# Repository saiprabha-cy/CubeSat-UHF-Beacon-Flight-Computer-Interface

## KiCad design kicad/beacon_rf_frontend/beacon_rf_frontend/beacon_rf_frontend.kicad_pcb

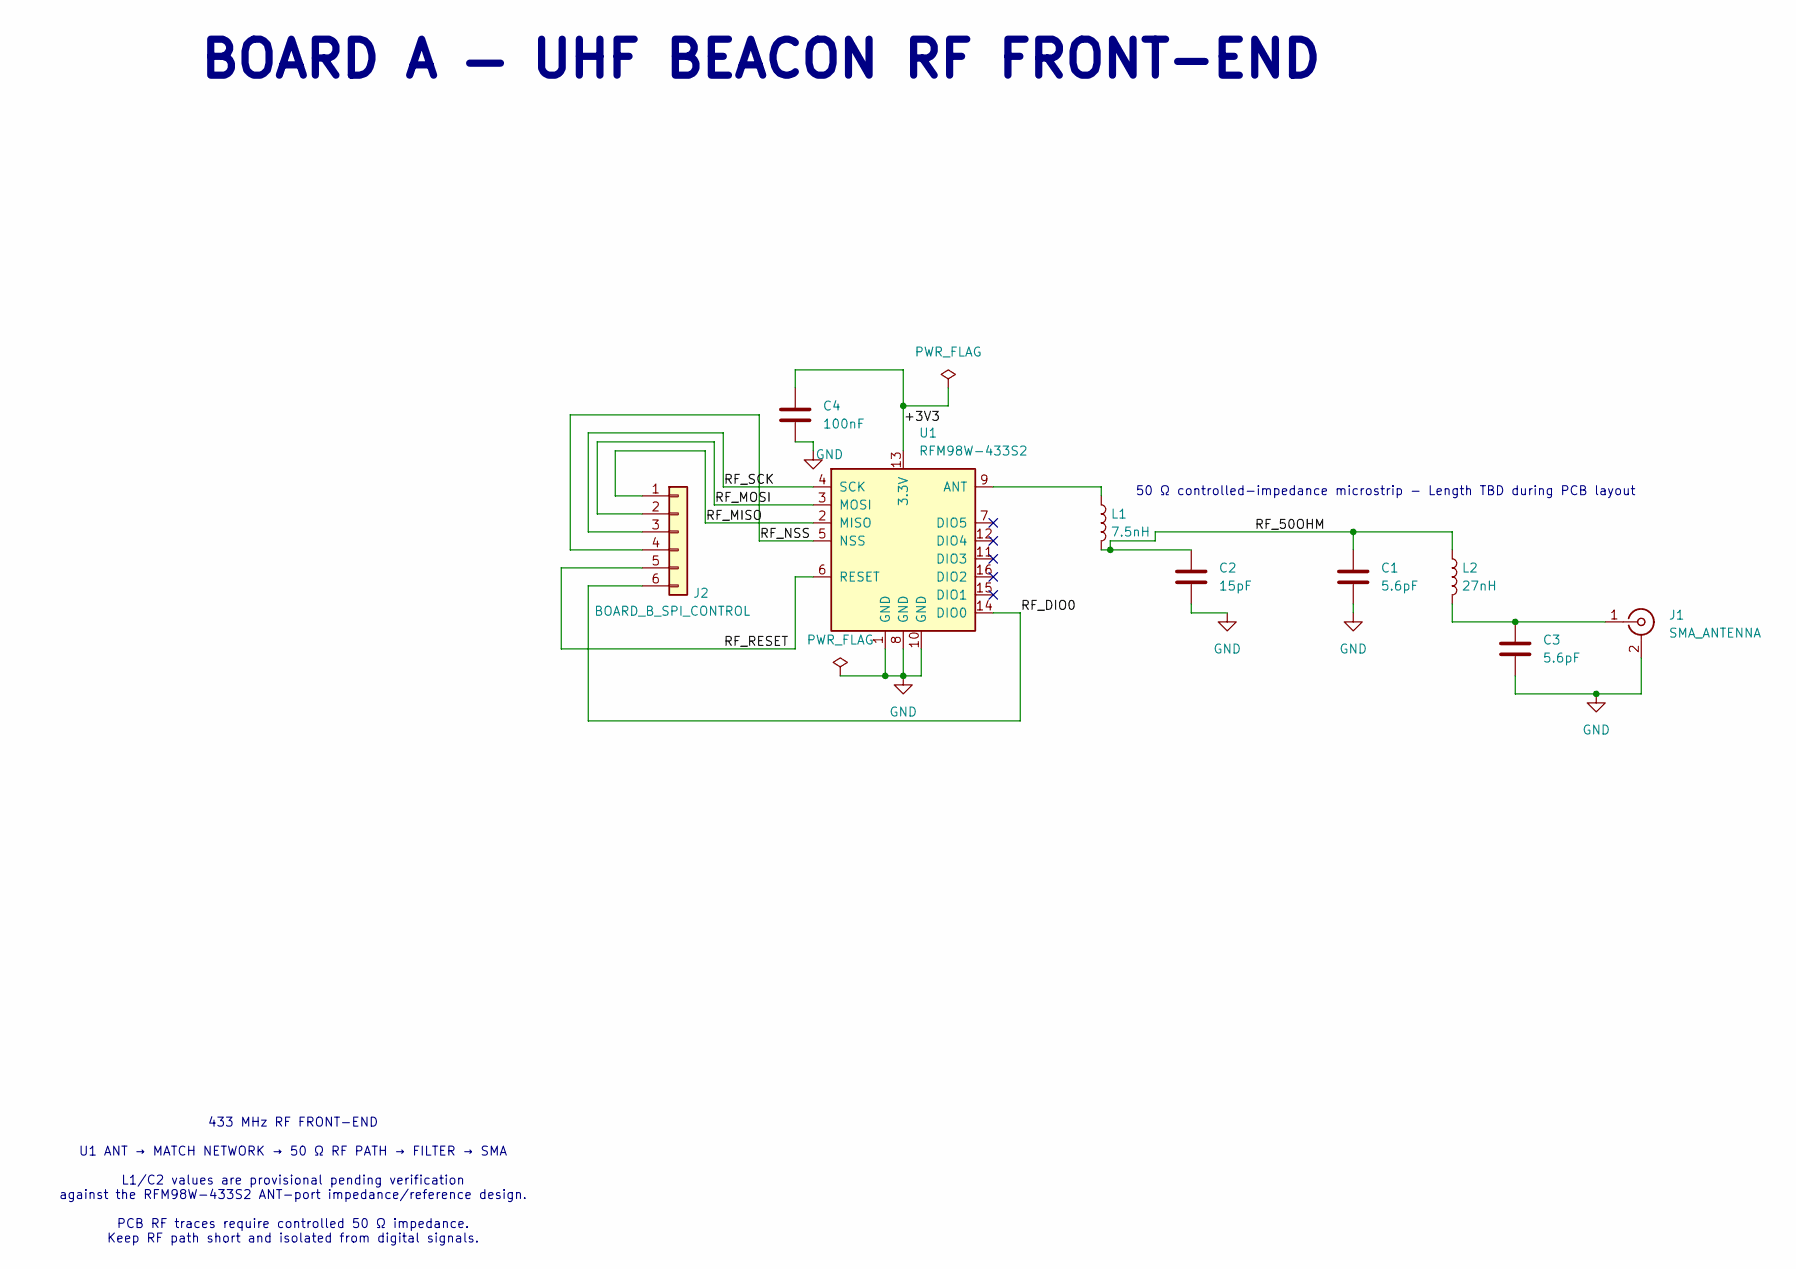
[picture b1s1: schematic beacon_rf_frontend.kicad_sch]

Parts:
C1, C3: 5.6pF; C_0402_1005Metric
C2: 15pF; C_0402_1005Metric
C4: 100nF; C_0603_1608Metric
J1: SMA_ANTENNA; SMA_Molex_73251-1153_EdgeMount_Horizontal
J2: BOARD_B_SPI_CONTROL; PinHeader_1x06_P2.54mm_Vertical
L1: 7.5nH; L_0402_1005Metric
L2: 27nH; L_0603_1608Metric
U1: RFM98W-433S2; HOPERF_RFM9XW_THT

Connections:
/+3V3: C4.1, U1.13 (3.3V)
/RF_50OHM: C1.1, C2.1, L1.2, L2.1
/RF_DIO0: J2.6, U1.14 (DIO0)
/RF_MISO: J2.1, U1.2 (MISO)
/RF_MOSI: J2.2, U1.3 (MOSI)
/RF_NSS: J2.4, U1.5 (NSS)
/RF_RESET: J2.5, U1.6 (RESET)
/RF_SCK: J2.3, U1.4 (SCK)
GND: C1.2, C2.2, C3.2, C4.2, J1.2 (Ext), U1.1 (GND), U1.8 (GND), U1.10 (GND)
unnamed: C3.1, J1.1 (In), L2.2
unnamed: L1.1, U1.9 (ANT)

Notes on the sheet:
433 MHz RF FRONT-END U1 ANT → MATCH NETWORK → 50 Ω RF PATH → FILTER → SMA L1/C2 values are provisional pending verification against the RFM98W-433S2 ANT-port impedance/reference design. PCB RF traces require controlled 50 Ω impedance. Keep RF path short and isolated from digital signals.
BOARD A — UHF BEACON RF FRONT-END
50 Ω controlled-impedance microstrip - Length TBD during PCB layout

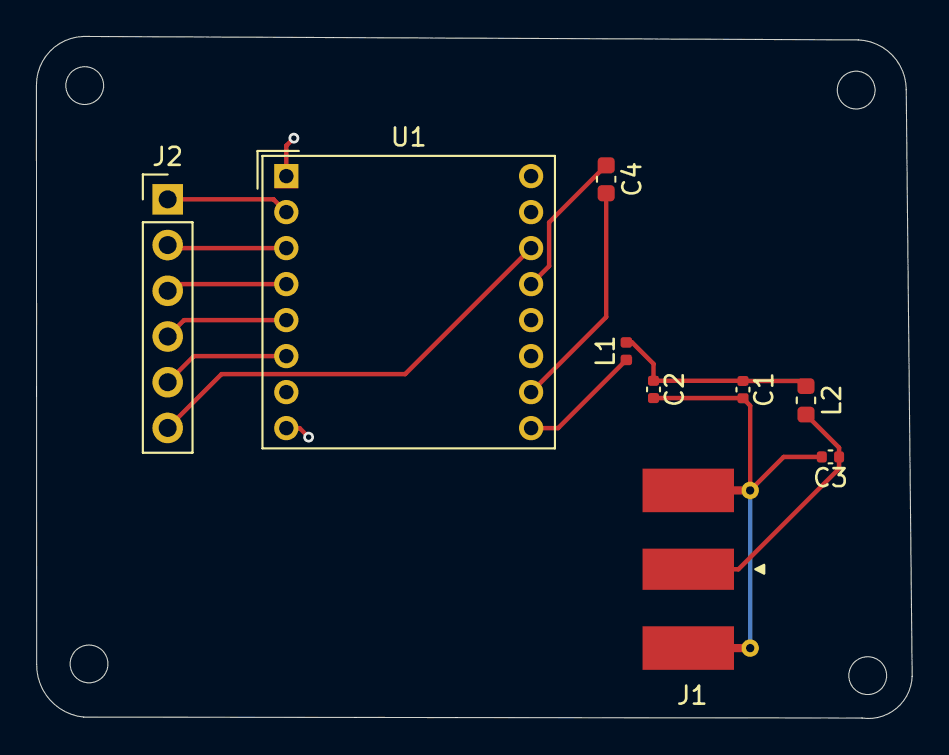
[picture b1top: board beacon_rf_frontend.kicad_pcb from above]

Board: 2 copper layers, 48.7 x 37.9 mm, 9 parts (0 on the bottom side), 11 nets.

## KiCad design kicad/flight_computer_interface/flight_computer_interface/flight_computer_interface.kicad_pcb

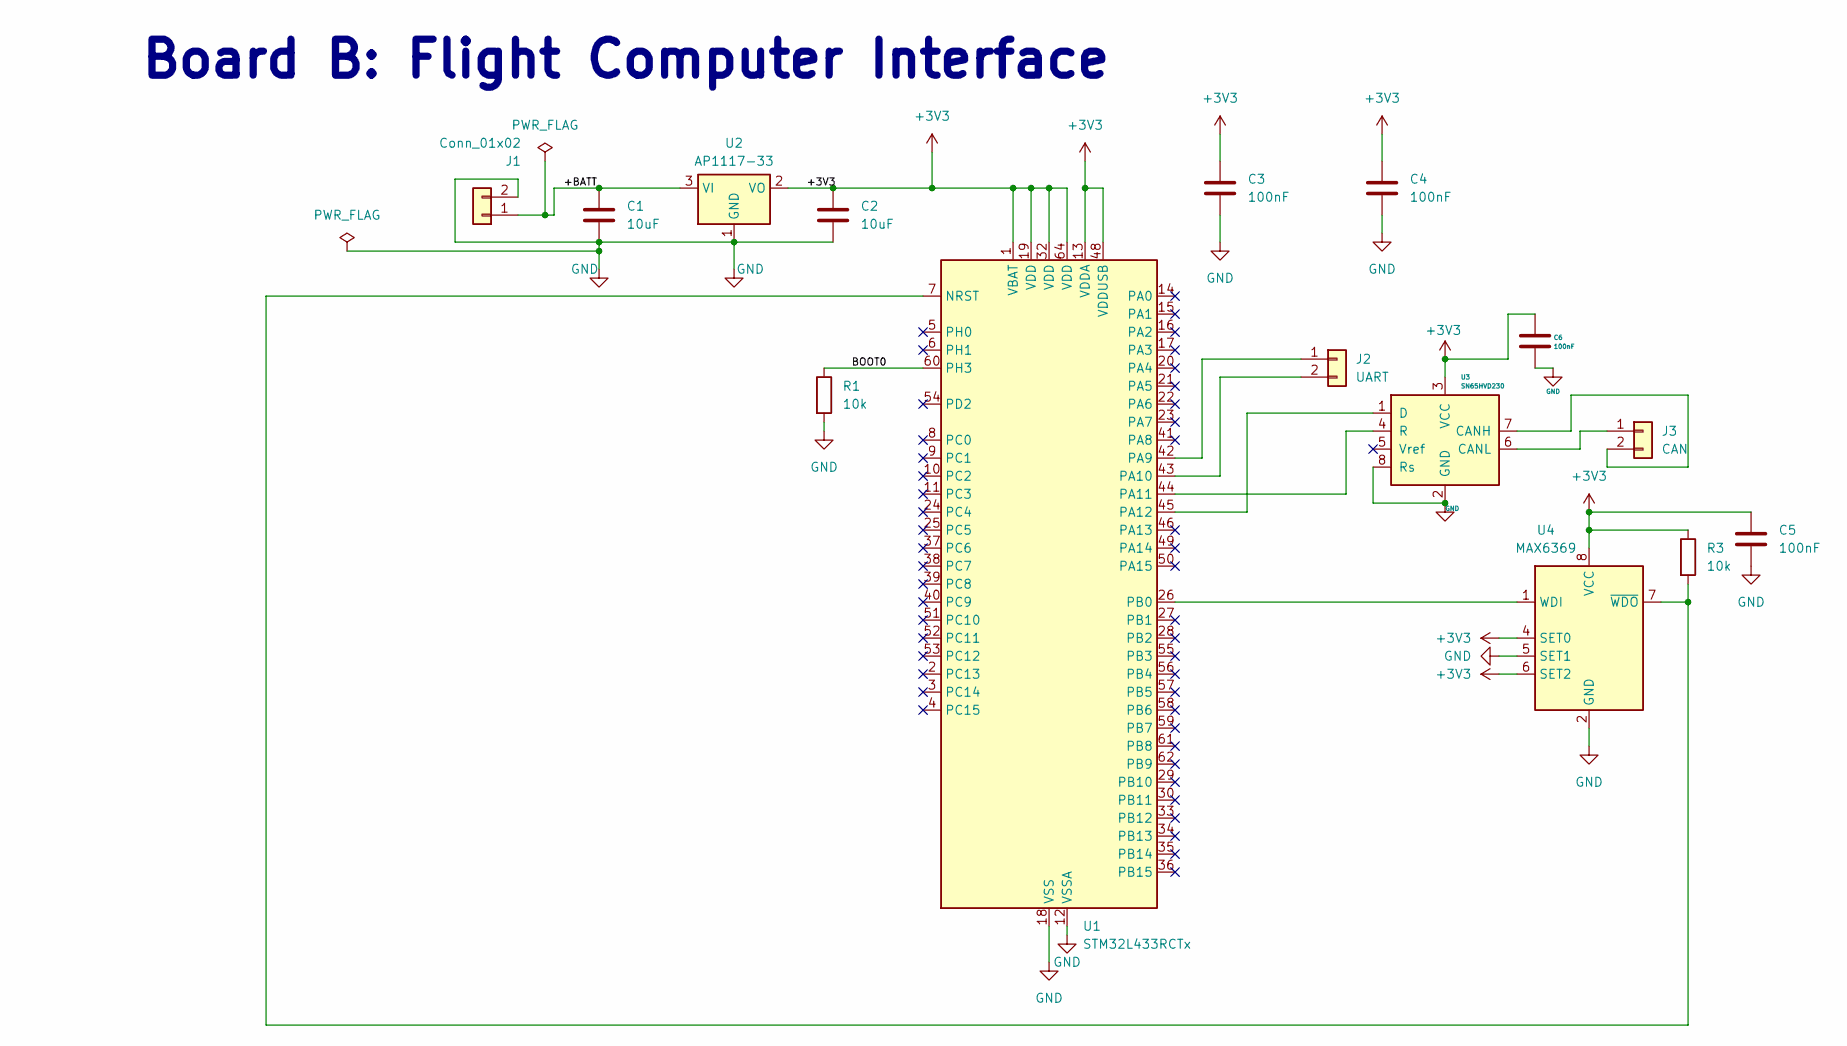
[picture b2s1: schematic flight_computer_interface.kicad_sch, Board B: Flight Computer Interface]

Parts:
C1, C2: 10uF; C_0805_2012Metric
C3, C4, C5, C6: 100nF; C_0603_1608Metric
J1: Conn_01x02; PinHeader_1x02_P2.54mm_Vertical
J2: UART; PinHeader_1x02_P2.54mm_Vertical
J3: CAN; PinHeader_1x02_P2.54mm_Vertical
R1, R3: 10k; R_0603_1608Metric
U1: STM32L433RCTx; LQFP-64_10x10mm_P0.5mm
U2: AP1117-33; SOT-223-3_TabPin2
U3: SN65HVD230; SOIC-8_3.9x4.9mm_P1.27mm
U4: MAX6369; SOT-23-8

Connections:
+3V3: C2.1, C3.1, C4.1, C5.1, C6.1, R3.1, U1.1 (VBAT), U1.13 (VDDA), U1.19 (VDD), U1.32 (VDD), U1.48 (VDDUSB), U1.64 (VDD), U2.2 (VO), U3.3 (VCC), U4.4 (SET0), U4.6 (SET2), U4.8 (VCC)
/+BATT: C1.1, J1.1, U2.3 (VI)
/BOOT0: R1.1, U1.60 (PH3)
GND: C1.2, C2.2, C3.2, C4.2, C5.2, C6.2, J1.2, R1.2, U1.12 (VSSA), U1.18 (VSS), U1.31 (VSS), U1.47 (VSS), U1.63 (VSS), U2.1 (GND), U3.2 (GND), U3.8 (Rs), U4.2 (GND), U4.5 (SET1)
unnamed: J2.1, U1.42 (PA9)
unnamed: J2.2, U1.43 (PA10)
unnamed: J3.1, U3.6 (CANL)
unnamed: J3.2, U3.7 (CANH)
unnamed: R3.2, U1.7 (NRST), U4.7 (~WDO)
unnamed: U1.44 (PA11), U3.4 (R)
unnamed: U1.45 (PA12), U3.1 (D)
unnamed: U1.26 (PB0), U4.1 (WDI)

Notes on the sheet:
Board B: Flight Computer Interface

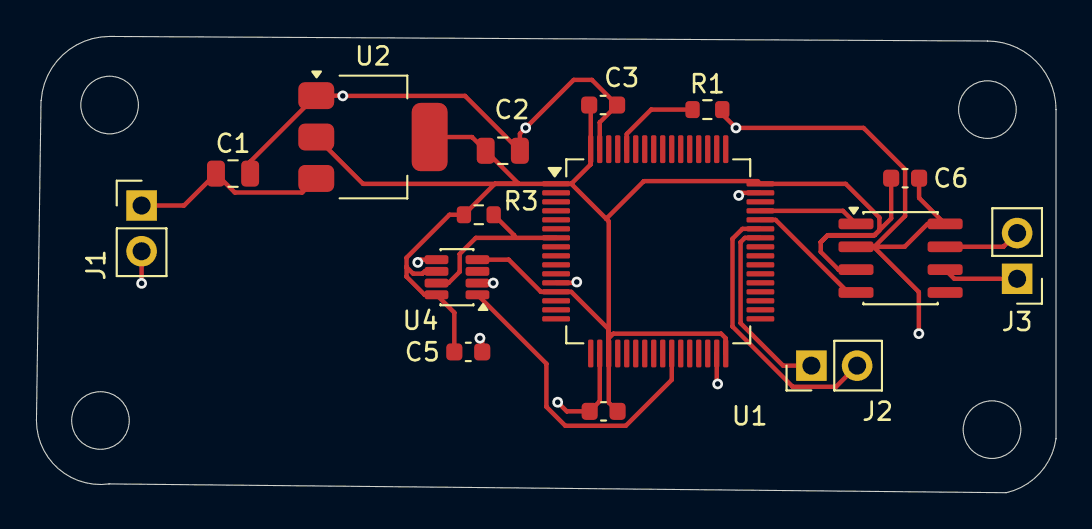
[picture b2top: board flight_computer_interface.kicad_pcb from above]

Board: 2 copper layers, 56.6 x 25.3 mm, 15 parts (0 on the bottom side), 12 nets.
